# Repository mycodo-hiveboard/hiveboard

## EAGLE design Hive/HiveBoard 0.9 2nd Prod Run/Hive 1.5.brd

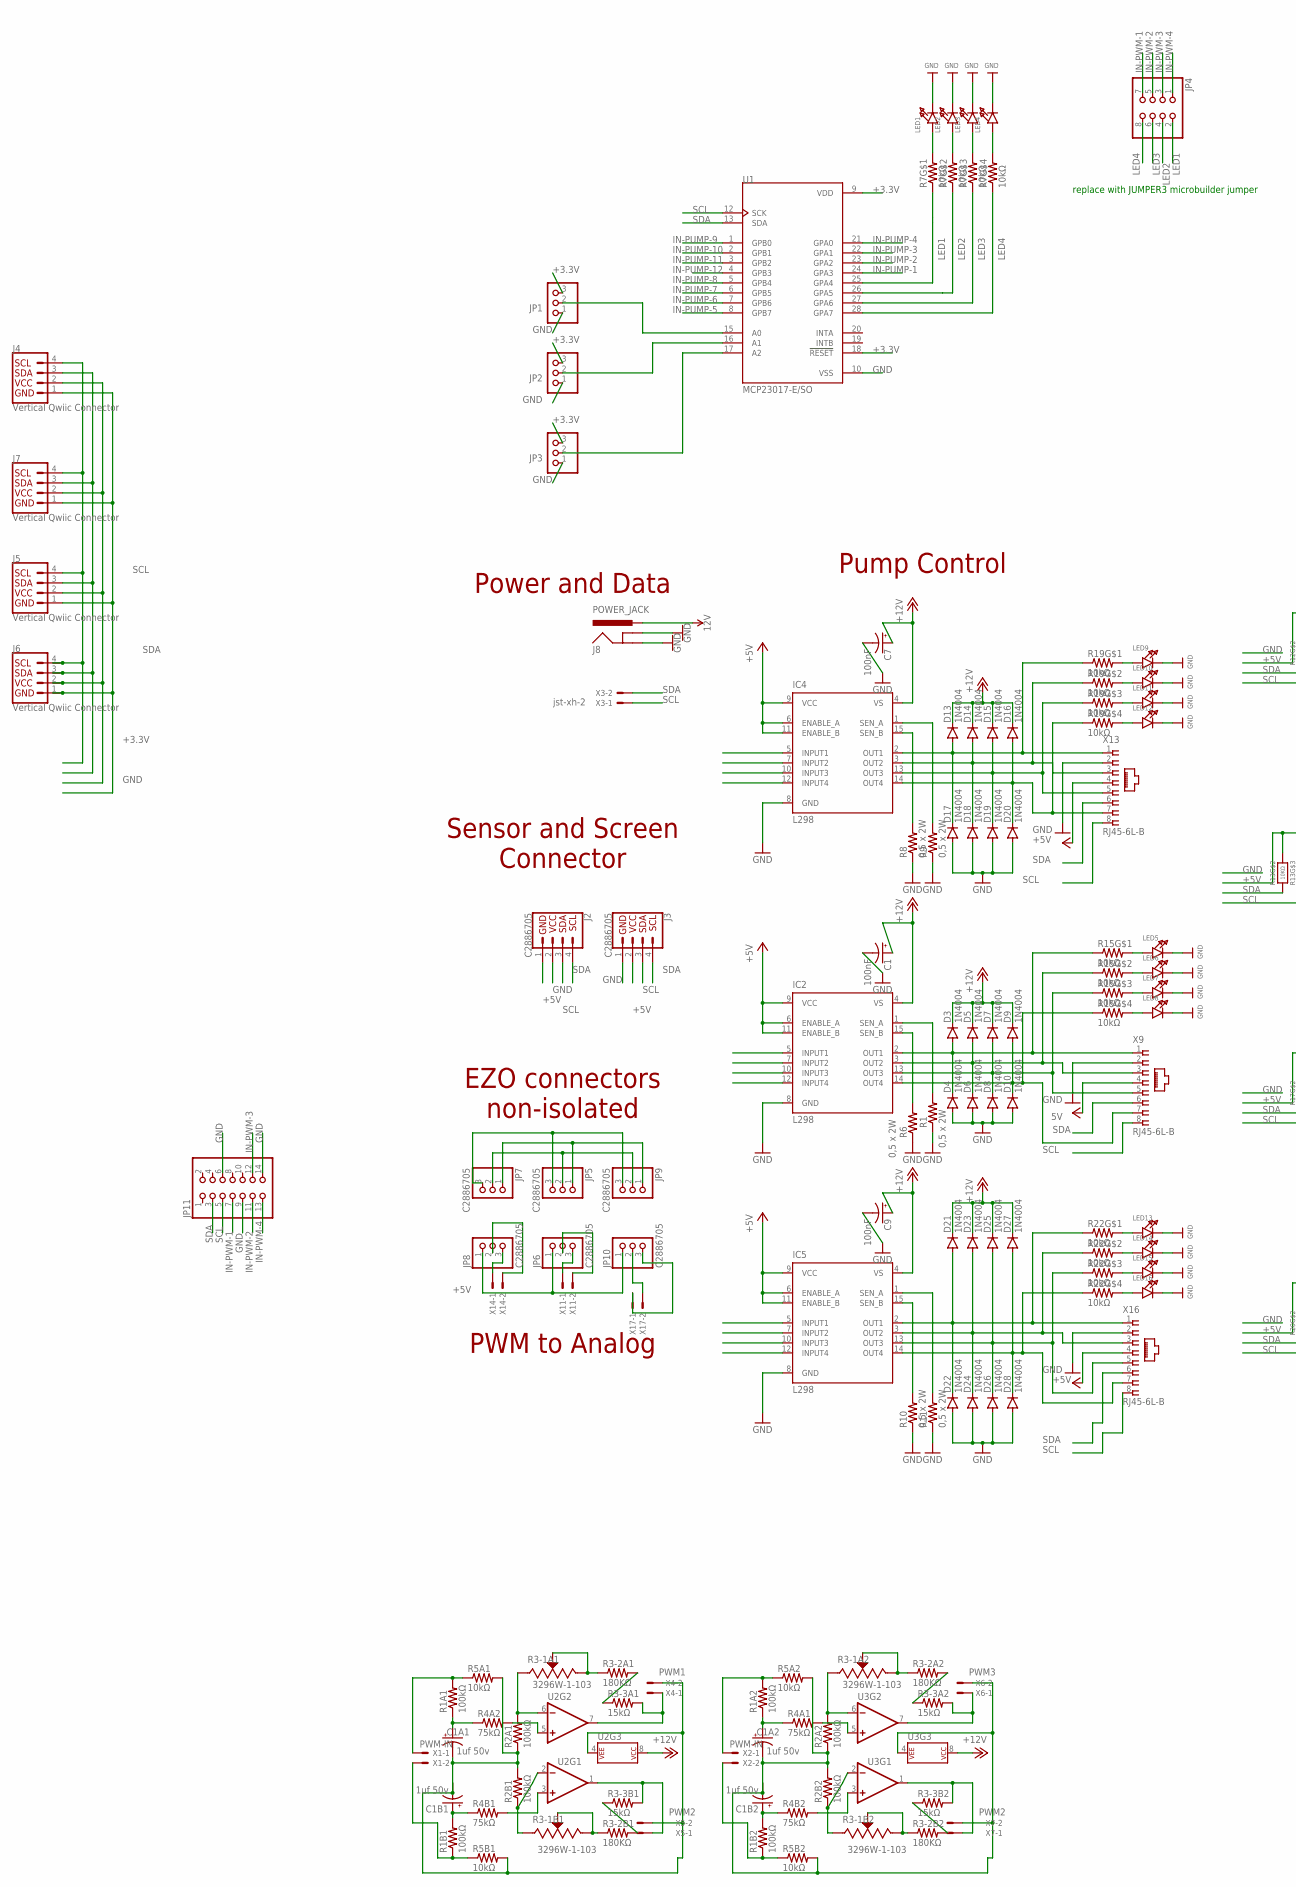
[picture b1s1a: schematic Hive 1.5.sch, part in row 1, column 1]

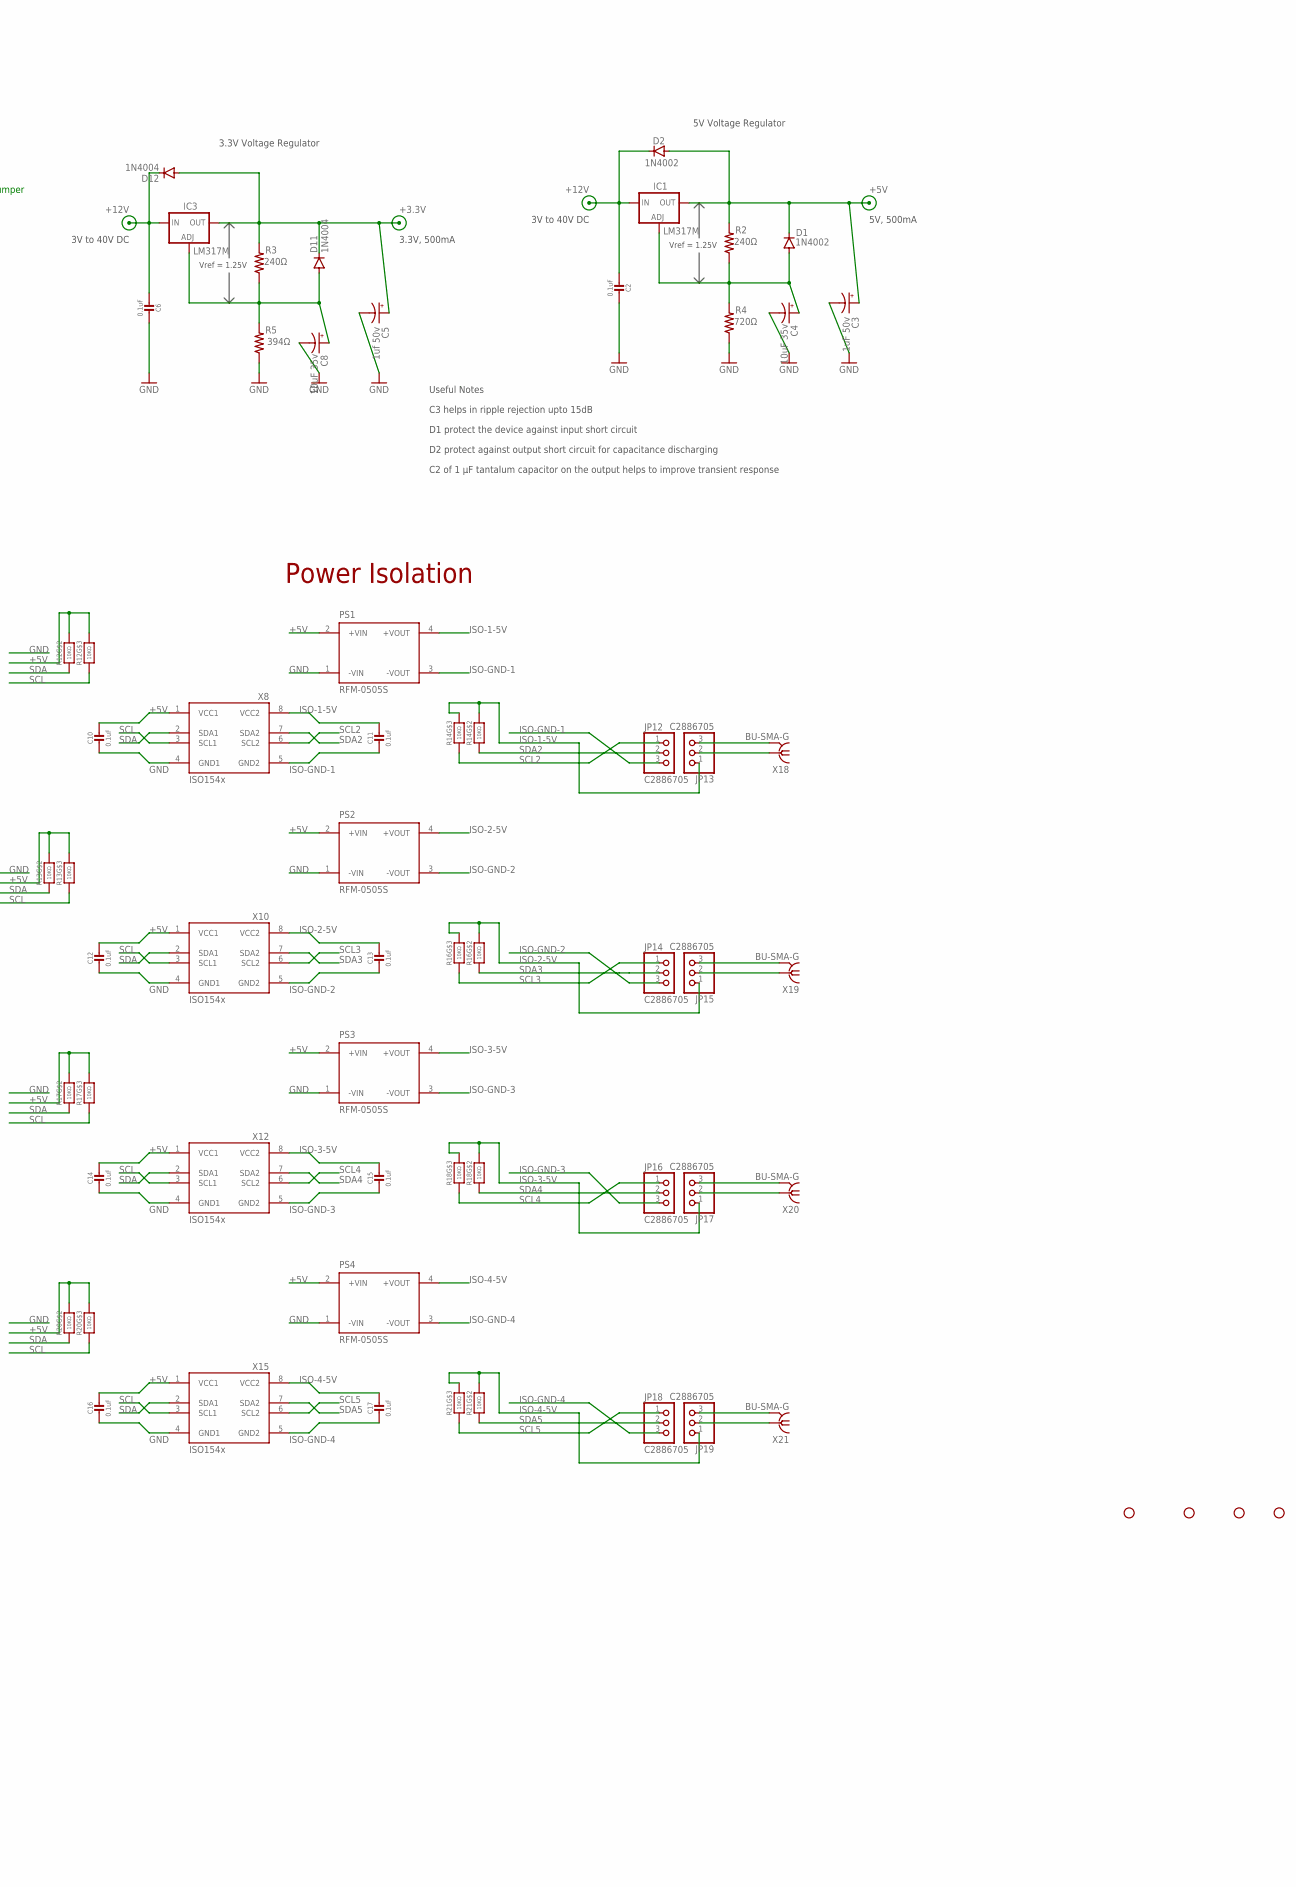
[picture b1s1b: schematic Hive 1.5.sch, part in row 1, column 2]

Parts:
C1, C7, C9: 100nF; UD-4X5,8_NICHICON
C1A1, C1A2, C1B1, C1B2, C5: 1uf 50v; UD-4X5,8_NICHICON
C2, C6, C10, C11, C12, C13, C14, C15, C16, C17: 0.1uF; 0603-NO
C3: 1uF 50v; UD-4X5,8_NICHICON
C4, C8: 10uF 35v; UD-4X5,8_NICHICON
D1, D2: 1N4002; DO214BA
D3, D4, D5, D6, D7, D8, D9, D10, D11, D12, D13, D14, D15, D16, D17, D18, D19, D20, D21, D22, D23, D24, D25, D26, D27, D28: 1N4004; DO214BA
H1, H2, H3, H4: STAND-OFF
IC1, IC3: LM317MBSTT3; SOT223; PARTNUMBER LM317M
IC2, IC4, IC5: L298; MULTIWATT-15
J2, J3: C2886705; 1X04
J4, J5, J6, J7: Vertical Qwiic Connector; JST04_1MM_VERT
J8: POWER_JACK; POWER_JACK_PTH
JP1, JP2, JP3: HEADER-1X3ROUND; 1X03_ROUND
JP4: PINHD-2X4; 2X04
JP5, JP6, JP7, JP8, JP9, JP10, JP12, JP13, JP14, JP15, JP16, JP17, JP18, JP19: C2886705; 1X03-CLEANBIG
JP11: PINHD-2X7; 2X07
LED1, LED2, LED3, LED4, LED5, LED6, LED7, LED8, LED9, LED10, LED11, LED12, LED13, LED14, LED15, LED16: LED0603; CHIPLED_0603
PS1, PS2, PS3, PS4: RFM-0505S; CONV_RFM-0505S
R1, R6, R8, R9, R10, R11: 0,5 x 2W; R2512
R1A1, R1A2, R1B1, R1B2, R2A1, R2A2, R2B1, R2B2: 100kΩ; M1206
R2, R3: 240Ω; M0805
R3-1A1, R3-1A2, R3-1B1, R3-1B2: 3296W-1-103; TRIM_3296W-1-103
R3-2A1, R3-2A2, R3-2B1, R3-2B2: 180KΩ; M1206
R3-3A1, R3-3A2, R3-3B1, R3-3B2: 15kΩ; M1206
R4: 720Ω; M0805
R4A1, R4A2, R4B1, R4B2: 75kΩ; M1206
R5: 394Ω; M0805
R5A1, R5A2, R5B1, R5B2: 10kΩ; M1206
R7, R15, R19, R22: 10kΩ; RESPACK_4X0603
R12, R13, R14, R16, R17, R18, R20, R21: 10KΩ; RESPACK_4X0603
U1: MCP23017-E/SO; SOIC127P1030X265-28N
U2, U3: LM358; SO08
X1, X2: PWM-IN; JST-XH-02-PACKAGE-LONG-PAD
X3, X11, X14, X17: jst-xh-2; JST-XH-02-PACKAGE-LONG-PAD
X4: PWM1; JST-XH-02-PACKAGE-LONG-PAD
X5, X7: PWM2; JST-XH-02-PACKAGE-LONG-PAD
X6: PWM3; JST-XH-02-PACKAGE-LONG-PAD
X8, X10, X12, X15: ISO154X; SOIC8_150MIL
X9, X13, X16: RJ45-6L-B; RJ45-NO-SHIELD
X18, X19, X20, X21: BU-SMA-G

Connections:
12V: J8.PWR
+3.3V: C5.+, D11.C, D12.A, IC3.4 (OUT), J4.2, J5.2, J6.2, J7.2, JP1.3, JP2.3, JP3.3, R3.2, U1.9 (VDD), U1.18 (!RESET)
+5V: C3.+, C10.1, C12.1, C14.1, C16.1, D1.C, D2.A, IC1.4 (OUT), IC2.6 (ENABLE_A), IC2.9 (VCC), IC2.11 (ENABLE_B), IC4.6 (ENABLE_A), IC4.9 (VCC), IC4.11 (ENABLE_B), IC5.6 (ENABLE_A), IC5.9 (VCC), IC5.11 (ENABLE_B), J2.1, J3.2, JP6.1, JP8.1, JP10.1, PS1.2 (+VIN), PS2.2 (+VIN), PS3.2 (+VIN), PS4.2 (+VIN), R2.2, R12.6 (2), R12.7 (2), R13.6 (2), R13.7 (2), R17.6 (2), R17.7 (2), R20.6 (2), R20.7 (2), X8.1 (VCC1), X9.4, X10.1 (VCC1), X12.1 (VCC1), X13.4, X15.1 (VCC1), X16.4
+12V: C1.+, C2.2, C6.2, C7.+, C9.+, D2.C, D3.C, D5.C, D7.C, D9.C, D12.C, D13.C, D14.C, D15.C, D16.C, D21.C, D23.C, D25.C, D27.C, IC1.3 (IN), IC2.4 (VS), IC3.3 (IN), IC4.4 (VS), IC5.4 (VS), U2.8 (P$V+), U3.8 (P$V+)
GND: C1.-, C1A1.-, C1A2.-, C1B1.-, C1B2.-, C2.1, C3.-, C4.-, C5.-, C6.1, C7.-, C8.-, C9.-, C10.2, C12.2, C14.2, C16.2, D4.A, D6.A, D8.A, D10.A, D17.A, D18.A, D19.A, D20.A, D22.A, D24.A, D26.A, D28.A, IC2.8 (GND), IC4.8 (GND), IC5.8 (GND), J2.2, J3.1, J4.1, J5.1, J6.1, J7.1, J8.GND, J8.GNDBREAK, JP1.1, JP2.1, JP3.1, JP5.3, JP7.3, JP9.3, JP11.6, JP11.9, JP11.14, LED1.C, LED2.C, LED3.C, LED4.C, LED5.C, LED6.C, LED7.C, LED8.C, LED9.C, LED10.C, LED11.C, LED12.C, LED13.C, LED14.C, LED15.C, LED16.C, PS1.1 (-VIN), PS2.1 (-VIN), PS3.1 (-VIN), PS4.1 (-VIN), R1.1, R2A1.1, R2A2.1, R2B1.2, R2B2.2, R4.1, R5.1, R5A1.2, R5A2.2, R5B1.2, R5B2.2, R6.1, R8.1, R9.1, R10.1, R11.1, U1.10 (VSS), U2.4 (P$V-), U3.4 (P$V-), X4.2, X5.2, X6.2, X7.2, X8.4 (GND1), X9.2, X10.4 (GND1), X12.4 (GND1), X13.2, X15.4 (GND1), X16.2
IN-PUMP-1: IC2.5 (INPUT1), U1.24 (GPA3)
IN-PUMP-2: IC2.7 (INPUT2), U1.23 (GPA2)
IN-PUMP-3: IC2.10 (INPUT3), U1.22 (GPA1)
IN-PUMP-4: IC2.12 (INPUT4), U1.21 (GPA0)
IN-PUMP-5: IC4.5 (INPUT1), U1.8 (GPB7)
IN-PUMP-6: IC4.7 (INPUT2), U1.7 (GPB6)
IN-PUMP-7: IC4.10 (INPUT3), U1.6 (GPB5)
IN-PUMP-8: IC4.12 (INPUT4), U1.5 (GPB4)
IN-PUMP-9: IC5.5 (INPUT1), U1.1 (GPB0)
IN-PUMP-10: IC5.7 (INPUT2), U1.2 (GPB1)
IN-PUMP-11: IC5.10 (INPUT3), U1.3 (GPB2)
IN-PUMP-12: IC5.12 (INPUT4), U1.4 (GPB3)
IN-PWM-1: JP4.7, JP11.7, R1A1.2, R5A1.1, X1.1
IN-PWM-2: JP4.5, JP11.11, R1B1.1, R5B1.1, X1.2
IN-PWM-3: JP4.3, JP11.12, R1A2.2, R5A2.1, X2.1
IN-PWM-4: JP4.1, JP11.13, R1B2.1, R5B2.1, X2.2
ISO-1-5V: C11.1, JP13.1, PS1.4 (+VOUT), R14.6 (2), R14.7 (2), X8.8 (VCC2)
ISO-2-5V: C13.1, JP15.1, PS2.4 (+VOUT), R16.6 (2), R16.7 (2), X10.8 (VCC2)
ISO-3-5V: C15.1, JP17.1, PS3.4 (+VOUT), R18.6 (2), R18.7 (2), X12.8 (VCC2)
ISO-4-5V: C17.1, JP19.1, PS4.4 (+VOUT), R21.6 (2), R21.7 (2), X15.8 (VCC2)
ISO-GND-1: C11.2, JP12.3, PS1.3 (-VOUT), X8.5 (GND2)
ISO-GND-2: C13.2, JP14.3, PS2.3 (-VOUT), X10.5 (GND2)
ISO-GND-3: C15.2, JP16.3, PS3.3 (-VOUT), X12.5 (GND2)
ISO-GND-4: C17.2, JP18.3, PS4.3 (-VOUT), X15.5 (GND2)
ISO-PRB-1+: JP13.2, X18.1
ISO-PRB-1GND: JP13.3, X18.2, X18.3 (2), X18.4 (2), X18.5 (2)
ISO-PRB-2+: JP15.2, X19.1
ISO-PRB-2GND: JP15.3, X19.2, X19.3 (2), X19.4 (2), X19.5 (2)
ISO-PRB-3+: JP17.2, X20.1
ISO-PRB-3GND: JP17.3, X20.2, X20.3 (2), X20.4 (2), X20.5 (2)
ISO-PRB-4+: JP19.2, X21.1
ISO-PRB-4GND: JP19.3, X21.2, X21.3 (2), X21.4 (2), X21.5 (2)
LED1: JP4.2, R7.1, U1.25 (GPA4)
LED2: JP4.4, R7.2 (1), U1.26 (GPA5)
LED3: JP4.6, R7.3 (1), U1.27 (GPA6)
LED4: JP4.8, R7.4 (1), U1.28 (GPA7)
unnamed: IC4.1 (SEN_A), R9.2
unnamed: IC4.15 (SEN_B), R8.2
unnamed: IC5.1 (SEN_A), R11.2
unnamed: IC5.15 (SEN_B), R10.2
unnamed: C8.+, D11.A, IC3.1 (ADJ), R3.1, R5.2
unnamed: R2A1.2, R3-1A1.1 (CCW), U2.6 (-IN)
unnamed: LED1.A, R7.8 (2)
unnamed: R2B1.1, R3-1B1.1 (CCW), U2.2 (-IN)
unnamed: IC2.1 (SEN_A), R1.2
unnamed: IC2.15 (SEN_B), R6.2
unnamed: C4.+, D1.A, IC1.1 (ADJ), R2.1, R4.2
unnamed: LED2.A, R7.7 (2)
unnamed: R3-1B1.2 (WIPER), R3-1B1.3 (CW), R3-2B1.1
unnamed: R3-2B1.2, R3-3B1.1
unnamed: R3-1A1.2 (WIPER), R3-1A1.3 (CW), R3-2A1.1
unnamed: R3-2A1.2, R3-3A1.1
unnamed: C1A1.+, R1A1.1, R4A2.1
unnamed: C1B1.+, R1B1.2, R4B1.1
unnamed: LED13.A, R22.8 (2)
unnamed: LED14.A, R22.7 (2)
unnamed: R4A2.2, U2.5 (+IN)
unnamed: R4B1.2, U2.3 (+IN)
unnamed: R3-1B2.2 (WIPER), R3-1B2.3 (CW), R3-2B2.1
unnamed: LED15.A, R22.6 (2)
unnamed: LED16.A, R22.5 (2)
unnamed: LED8.A, R15.5 (2)
unnamed: LED7.A, R15.6 (2)
unnamed: LED6.A, R15.7 (2)
unnamed: LED5.A, R15.8 (2)
unnamed: LED9.A, R19.8 (2)
unnamed: LED10.A, R19.7 (2)
unnamed: LED11.A, R19.6 (2)
unnamed: LED12.A, R19.5 (2)
unnamed: LED3.A, R7.6 (2)
unnamed: LED4.A, R7.5 (2)
unnamed: R3-2B2.2, R3-3B2.1
unnamed: R3-1A2.2 (WIPER), R3-1A2.3 (CW), R3-2A2.1
unnamed: R3-2A2.2, R3-3A2.1
unnamed: C1A2.+, R1A2.1, R4A1.1
unnamed: C1B2.+, R1B2.2, R4B2.1
unnamed: R2A2.2, R3-1A2.1 (CCW), U3.6 (-IN)
unnamed: R2B2.1, R3-1B2.1 (CCW), U3.2 (-IN)
unnamed: R4A1.2, U3.5 (+IN)
unnamed: R4B2.2, U3.3 (+IN)
unnamed: JP1.2, U1.15 (A0)
unnamed: JP2.2, U1.16 (A1)
unnamed: JP3.2, U1.17 (A2)
NISO-PRB-1+: JP6.2, X11.2
NISO-PRB-1GND: JP6.3, X11.1
NISO-PRB-2+: JP8.2, X14.2
NISO-PRB-2GND: JP8.3, X14.1
NISO-PRB-3+: JP10.2, X17.2
NISO-PRB-3GND: JP10.3, X17.1
OUT-PUMP-1: D3.A, D4.C, IC2.2 (OUT1), R15.1, X9.1
OUT-PUMP-2: D5.A, D6.C, IC2.3 (OUT2), R15.2 (1), X9.3
OUT-PUMP-3: D7.A, D8.C, IC2.13 (OUT3), R15.3 (1), X9.5
OUT-PUMP-4: D9.A, D10.C, IC2.14 (OUT4), R15.4 (1), X9.7
OUT-PUMP-5: D13.A, D17.C, IC4.2 (OUT1), R19.1, X13.1
OUT-PUMP-6: D14.A, D18.C, IC4.3 (OUT2), R19.2 (1), X13.3
OUT-PUMP-7: D15.A, D19.C, IC4.13 (OUT3), R19.3 (1), X13.5
OUT-PUMP-8: D16.A, D20.C, IC4.14 (OUT4), R19.4 (1), X13.7
OUT-PUMP-9: D21.A, D22.C, IC5.2 (OUT1), R22.1, X16.1
OUT-PUMP-10: D23.A, D24.C, IC5.3 (OUT2), R22.2 (1), X16.3
OUT-PUMP-11: D25.A, D26.C, IC5.13 (OUT3), R22.3 (1), X16.5
OUT-PUMP-12: D27.A, D28.C, IC5.14 (OUT4), R22.4 (1), X16.7
PWM-OUT-1: R3-3A1.2, U2.7 (OUT), X4.1
PWM-OUT-2: R3-3B1.2, U2.1 (OUT), X5.1
PWM-OUT-3: R3-3A2.2, U3.7 (OUT), X6.1
PWM-OUT-4: R3-3B2.2, U3.1 (OUT), X7.1
SCL: J2.3, J3.3, J4.4, J5.4, J6.4, J7.4, JP5.1, JP7.1, JP9.1, JP11.5, R12.3 (1), R13.3 (1), R17.3 (1), R20.3 (1), U1.12 (SCK), X3.1, X8.3 (SCL1), X9.8, X10.3 (SCL1), X12.3 (SCL1), X13.8, X15.3 (SCL1), X16.8
SCL2: JP12.1, R14.3 (1), X8.6 (SCL2)
SCL3: JP14.1, R16.3 (1), X10.6 (SCL2)
SCL4: JP16.1, R18.3 (1), X12.6 (SCL2)
SCL5: JP18.1, R21.3 (1), X15.6 (SCL2)
SDA: J2.4, J3.4, J4.3, J5.3, J6.3, J7.3, JP5.2, JP7.2, JP9.2, JP11.3, R12.2 (1), R13.2 (1), R17.2 (1), R20.2 (1), U1.13 (SDA), X3.2, X8.2 (SDA1), X9.6, X10.2 (SDA1), X12.2 (SDA1), X13.6, X15.2 (SDA1), X16.6
SDA2: JP12.2, R14.2 (1), X8.7 (SDA2)
SDA3: JP14.2, R16.2 (1), X10.7 (SDA2)
SDA4: JP16.2, R18.2 (1), X12.7 (SDA2)
SDA5: JP18.2, R21.2 (1), X15.7 (SDA2)

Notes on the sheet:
Power Isolation
Pump Control
PWM to Analog
EZO connectors non-isolated
Sensor and Screen Connector
Power and Data
3.3V Voltage Regulator
C3 helps in ripple rejection upto 15dB
D1 protect the device against input short circuit
D2 protect against output short circuit for capacitance discharging
C2 of 1 µF tantalum capacitor on the output helps to improve transient response
Useful Notes
3V to 40V DC
Vref = 1.25V
3.3V, 500mA
5V Voltage Regulator
5V, 500mA
replace with JUMPER3 microbuilder jumper

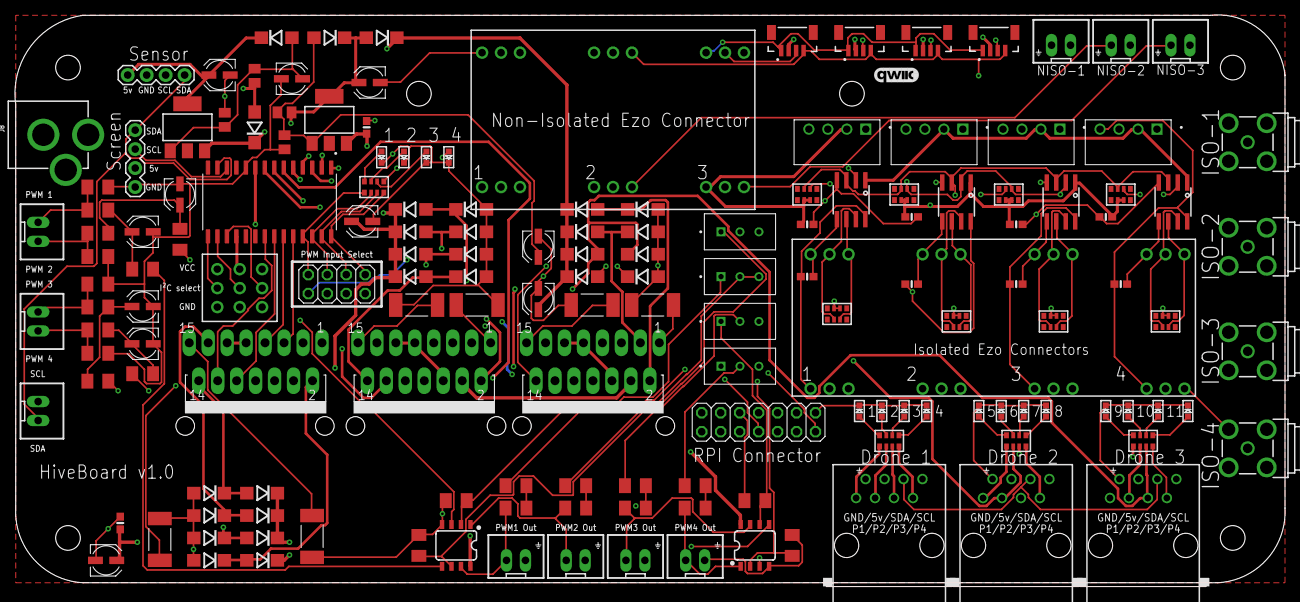
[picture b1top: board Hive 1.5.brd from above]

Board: 4 copper layers, 170.1 x 76.6 mm, 181 parts (0 on the bottom side), 119 nets.

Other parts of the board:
U$1, U$4: STAND-OFF
U$2: QWIIC_6MM

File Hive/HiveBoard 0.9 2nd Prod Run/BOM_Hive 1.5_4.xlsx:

No. | Quantity | Comment | Designator | Footprint | Value | Manufacturer Part | Manufacturer | Supplier Part | Supplier
1 | 3 | 100nF | C1,C7,C9 | UD-4X5,8_NICHICON | C271438
2 | 5 | 1uf 50v | C1A1,C1A2,C1B1,C1B2,C5 | UD-4X5,8_NICHICON | C3348
3 | 10 | 0.1uF | C2,C6,C10,C11,C12,C13,C14,C15,C16,C17 | 0603-NO
4 | 1 | 1uF 50v | C3 | UD-4X5,8_NICHICON | C3348
5 | 2 | 10uF 35v | C4,C8 | UD-4X5,8_NICHICON | C72485
6 | 2 | 1N4002 | D1,D2 | DO214BA
7 | 26 | 1N4004 | D3,D4,D5,D6,D7,D8,D9,D10,D11,D12,D13,D14,D15,D16,D17,D18,D19,D20,D21,D22,D23,D2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 | DO214BA
8 | 4 | STAND-OFF | H1,H2,H3,H4 | STAND-OFF
9 | 2 | LM317MBSTT3 | IC1,IC3 | SOT223
10 | 3 | L298 | IC2,IC4,IC5 | MULTIWATT-15
11 | 2 | C2886705 | J2,J3 | 1X04 | C2718488
12 | 4 | Vertical Qwiic Connector | J4,J5,J6,J7 | JST04_1MM_VERT | C2859067
13 | 1 | POWER_JACK | J8 | POWER_JACK_PTH | C16214
14 | 3 |  | JP1,JP2,JP3 | 1X03_ROUND | C49257
15 | 1 |  | JP4 | 2X04 | C124386
16 | 14 | C2886705 | JP5,JP6,JP7,JP8,JP9,JP10,JP12,JP13,JP14,JP15,JP16,JP17,JP18,JP19 | 1X03-CLEANBIG | C2932670
17 | 1 |  | JP11 | 2X07 | C71397
18 | 16 |  | LED1,LED2,LED3,LED4,LED5,LED6,LED7,LED8,LED9,LED10,LED11,LED12,LED13,LED14,LED1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 | CHIPLED_0603 | C84266
19 | 4 | RFM-0505S | PS1,PS2,PS3,PS4 | CONV_RFM-0505S
20 | 6 | 0,5 x 2W | R1,R6,R8,R9,R10,R11 | R2512 | C469426
21 | 8 | 100kΩ | R1A1,R1A2,R1B1,R1B2,R2A1,R2A2,R2B1,R2B2 | M1206
22 | 2 | 240Ω | R2,R3 | M0805
23 | 4 | 3296W-1-103 | R3-1A1,R3-1A2,R3-1B1,R3-1B2 | TRIM_3296W-1-103
24 | 4 | 180KΩ | R3-2A1,R3-2A2,R3-2B1,R3-2B2 | M1206
25 | 4 | 15kΩ | R3-3A1,R3-3A2,R3-3B1,R3-3B2 | M1206
26 | 1 | 720Ω | R4 | M0805 | c17813
27 | 4 | 75kΩ | R4A1,R4A2,R4B1,R4B2 | M1206 | C17986
28 | 1 | 394Ω | R5 | M0805
29 | 4 | 10kΩ | R5A1,R5A2,R5B1,R5B2 | M1206
30 | 4 | 10kΩ | R7,R15,R19,R22 | RESPACK_4X0603 | C29718
31 | 8 | 10KΩ | R12,R13,R14,R16,R17,R18,R20,R21 | RESPACK_4X0603 | C29718
32 | 1 | MCP23017-E/SO | U1 | SOIC127P1030X265-28N | C629440
33 | 2 | LM358 | U2,U3 | SO08
34 | 2 |  | U$1,U$4 | STAND-OFF
35 | 1 |  | U$2 | QWIIC_6MM
36 | 2 | PWM-IN | X1,X2 | JST-XH-02-PACKAGE-LONG-PAD
37 | 4 | jst-xh-2 | X3,X11,X14,X17 | JST-XH-02-PACKAGE-LONG-PAD
38 | 1 | PWM1 | X4 | JST-XH-02-PACKAGE-LONG-PAD
39 | 2 | PWM2 | X5,X7 | JST-XH-02-PACKAGE-LONG-PAD
40 | 1 | PWM3 | X6 | JST-XH-02-PACKAGE-LONG-PAD
41 | 4 | ISO154X | X8,X10,X12,X15 | SOIC8_150MIL
42 | 3 | RJ45-6L-B | X9,X13,X16 | RJ45-NO-SHIELD
43 | 4 | BU-SMA-G | X18,X19,X20,X21 | BU-SMA-G | C914553

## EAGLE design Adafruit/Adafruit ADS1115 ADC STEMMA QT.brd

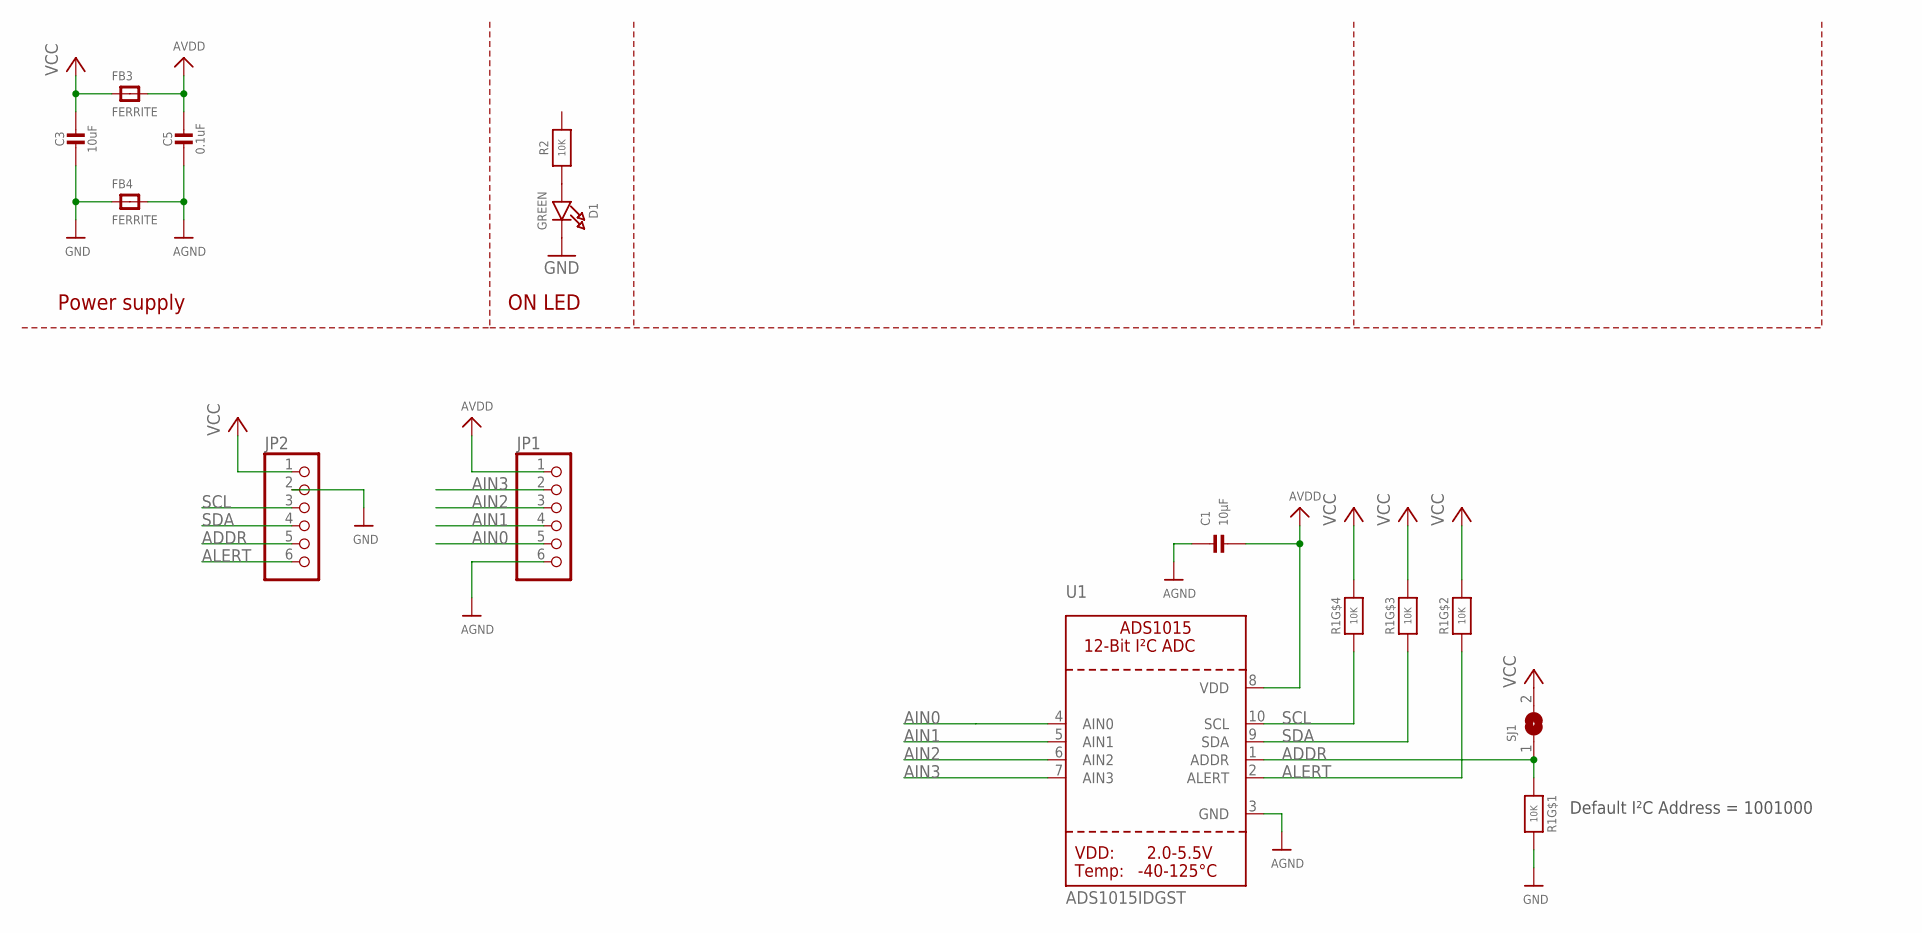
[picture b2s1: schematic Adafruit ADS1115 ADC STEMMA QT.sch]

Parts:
C1: 10µF; 0805-NO
C3: 10uF; 0805-NO
C5: 0.1uF; 0603-NO
D1: GREEN; CHIPLED_0603_NOOUTLINE
FB3, FB4: FERRITE; 0603-NO
JP1, JP2: HEADER-1X670MIL; 1X06_ROUND_70
R1: 10K; RESPACK_4X0603
R2: 10K; 0603-NO
SJ1: SOLDERJUMPER; SOLDERJUMPER_ARROW_NOPASTE
U1: ADS1015IDGST; MSOP10

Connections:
ADDR: JP2.5, R1.1, SJ1.1, U1.1 (ADDR)
AGND: C1.1, C5.2, FB4.2, JP1.6, U1.3 (GND)
AIN0: JP1.5, U1.4 (AIN0)
AIN1: JP1.4, U1.5 (AIN1)
AIN2: JP1.3, U1.6 (AIN2)
AIN3: JP1.2, U1.7 (AIN3)
ALERT: JP2.6, R1.2 (1), U1.2 (ALERT)
AVDD: C1.2, C5.1, FB3.2, JP1.1, U1.8 (VDD)
GND: C3.2, D1.C, FB4.1, JP2.2, R1.8 (2)
unnamed: D1.A, R2.1
SCL: JP2.3, R1.4 (1), U1.10 (SCL)
SDA: JP2.4, R1.3 (1), U1.9 (SDA)
VCC: C3.1, FB3.1, JP2.1, R1.5 (2), R1.6 (2), R1.7 (2), SJ1.2

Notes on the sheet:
ON LED
Power supply
Default I²C Address = 1001000

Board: 2 copper layers, 13 parts (2 on the bottom side), 13 nets, no tracks yet.

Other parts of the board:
U$35: STEMMAQT

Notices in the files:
parts and their libraries:
microbuilder: This work is placed in the public domain, and may be freely used for commercial and non-commercial work with the following conditions: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
SparkFun-Connectors: Licensing: Creative Commons ShareAlike 4.0 International - https://creativecommons.org/licenses/by-sa/4.0
